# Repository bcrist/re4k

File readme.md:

# Fusemaps for Lattice ispMach4000 CPLDs

This repo contains reverse-engineered fusemaps for most of the commonly available LC4k CPLDs from Lattice.

Data is provided in text files containing machine and human readable S-Expressions describing the fuse locations that control each feature.
These are intended to be used to generate libraries so that CPLD configurations can be created using whatever programming language is desired.
Existing libraries include:

* Zig: [Zig-LC4k](https://github.com/bcrist/Zig-LC4k)
* VHDL: [LC4K Core](https://github.com/devsaurus/lc4k_core)

If you build a library/bindings for another language, let me know so I can list it here!

## Device List

|            |TQFP44|TQFP48|TQFP100|TQFP128|TQFP144|csBGA56|csBGA64|csBGA132|csBGA144|ucBGA64|ucBGA132|
|:-----------|:----:|:----:|:-----:|:-----:|:-----:|:-----:|:-----:|:------:|:------:|:-----:|:------:|
|LC4032V/B/C | ✔️    | ✔️    |       |       |       |       |       |        |        |       |        |
|LC4032ZC    |      | ✔️    |       |       |       | ✔️     |       |        |        |       |        |
|LC4032ZE    |      | ✔️    |       |       |       |       | ✔️     |        |        |       |        |
|LC4064V/B/C | ✔️    | ✔️    | ✔️     |       |       |       |       |        |        |       |        |
|LC4064ZC    |      | ✔️    | ✔️     |       |       | ✔️     |       | ✔️      |        |       |        |
|LC4064ZE    |      | ✔️    | ✔️     |       |       |       | ✔️     |        | ✔️      | ✔️     |        |
|LC4128V     |      |      | ✔️     | ✔️     | ✔️     |       |       |        |        |       |        |
|LC4128B/C   |      |      | ✔️     | ✔️     |       |       |       |        |        |       |        |
|LC4128ZC    |      |      | ✔️     |       |       |       |       | ✔️      |        |       |        |
|LC4128ZE    |      |      | ✔️     |       | ✔️     |       |       |        | ✔️      |       | ✔️      |

LC4256 and larger devices are not supported at this time.
Automotive (LA4xxx) variants likely use the same fusemaps as their LC counterparts, but that's just conjecture.
Please don't use this project for any automotive or other safety-critical application.

## Introduction
Please read through the Lattice datasheet for your device if you have not.
Generally I have tried to use the same terminology for things as is used there.
You can also reference the glossary at the end of this document if you are unsure of what an acronym or term means.
You can find PDF and KiCAD format schematics showing the structure of each type of device in the `schematics` directory.

## General Fusemap Layout
All LC4k devices have a logical layout of fuses into a 2D grid with either 100 or 95 rows,
and a variable number of columns, depending on the number of GLBs in the device.
The JEDEC files list these fuses one row after another,
and when programming the device via JTAG each row is delivered in a separate SDR transaction.

Each GLB uses a chunk of at least 86 columns,
and the GLBs are laid out side-by-side,
however they are not generally ordered from left to right
(the block for GLB "A" is not necessarily to the left of the block for GLB "B").

The first 72 rows contain PT and GI routing fuses.
This part of the fusemap is densely packed;
every single logical fuse corresponds to a bit of FLASH memory and controls the behavior of the device.

The remaining rows have a variety of uses, and are sparsely packed;
most bits don't actually correspond to FLASH memory cells, and always read as a `1`, even after attempting to program them to `0`.

Generally there is a single column corresponding to each macrocell slice, containing fuses that configure that macrocell slice.
These columns are arranged in groups of two, usually with 8 mostly-unused columns separating each pair.
Devices that only have 95 rows only have a single I/O cell per pair of macrocells.
Instead of placing all the I/O cell configuration fuses in the same column,
half of the fuses are shifted over to the adjacent macrocell's column,
reducing the total number of rows needed.

Each GLB has a few bits of block configuration which are placed in the "borders" to the left and right of the macrocell slice columns.
This includes fuses for configuring block clock source/polarity, shared PT polarity, routing of the shared PT enable to the GOE bus, etc.

Finally, global configuration is typically placed in a small, vaguely ring-shaped structure at the right edge of one of the GLB regions.
This includes configuration of input-only pins, GOE polarity, and oscillator/timer (in ZE devices).

## S-Expression Files
The reverse-engineered fusemap for each device consists of a set of s-expression files in `LC4xxx/LC4xxx*_*/.sx`.
There is also a combined file `LC4xxx/LC4xxx*_*.sx` which contains the data from all of the individual files.
The meaning of the data in each particular file is explained below.
If the syntax of any of the files is confusing to you after reading its corresponding section,
please open an issue so I can try to document it better.

### `grp.sx` `(global_routing_pool)`
Each GLB has 36 GI "slots" which (along with their complements) are used as inputs to the product terms in that GLB.
Each GI can be selected from a fixed set of signals in the global routing pool.
The options are different for each GI "slot" in the GLB,
but every GLB in the device uses the same options for the same GI slot.
The number of options for each slot depends on the device type
(devices with more GLBs have more GRP signals,
therefore in order to have multiple possible routings for each signal,
each GLB must have more possible options).

For devices that have an even number of GI options,
the option fuses are stored at the very left side of the GLB block,
using `N/2` columns (where `N` is the number of options).
A "one-cold" encoding is used here; i.e. there is one fuse for each option,
and only one fuse should be programmed to 0 for each GI.

For devices that have an odd number of GI options, the GLBs are organized into pairs,
and each pair shares the same columns of GI routing fuses.  The first row contains fuses
for one of the GLBs, and the second row contains fuses for the other.

### `pterms.sx` `(product_terms)`
Within the first 72 rows, each column
(with the exception of the columns used for GI routing above)
represents a single product term.
Every pair of rows corresponds to a single GI slot,
with the first row representing the non-inverted GI signal,
and the second row representing the inverted version of the same signal.

Programming a fuse within a product term to 0 means the corresponding signal must be asserted
in order for the product term to output `true`.
Another way to think of this is that the fuse value is OR-ed with the signal, and the result is
passed into the product term's AND gate.
Therefore if no PT fuses are set to 0, the PT will always yield `true`.
If both fuses are set to 0 for any GI, the PT will always yield `false`.
When the lpf4k fitter wants to make a PT `false`,
it sets all the fuses for the first dozen or so rowss to 0.
It's not clear why they chose to set just those.
It may be that setting just one pair to 0 might create static hazards
if the GI mapped to that slot changes.
But in that case wouldn't it be best to set all GI pairs to zeroes?
In testing, that does seem to work as expected,
so that's what I'd recommend doing.
My best guess is that this could be a holdover from older device families
that used sense amplifiers instead of fully CMOS logic.
Setting all fuses to 0 might cause higher power usage in such devices.

Product terms are grouped into clusters of 5,
with one cluster associated with each macrocell.
Additionally, there are 3 extra product terms per GLB,
which may be used for specific purposes,
but are shared amongst all macrocells in the GLB.
These PTs are always in the last 3 columns of the GLB's block.

### `cluster_routing.sx` `(cluster_routing)`
Each product term can optionally be used for a special purpose related to that macrocell (see below),
or they can be summed (OR-ed) together and fed into the macrocell's logic input.

Since a logic equation simplified to a sum-of-products often requires more than 5 product terms,
a cluster can either keep it's sum for itself,
or it can "donate" it to one of up to three nearby macrocells.
Each cluster then creates a second sum from any intermediate sums that were routed to that cluster.
A cluster can receive a "donation" (or multiple) even if it is not "keeping" it's own original sum.
Therefore this second sum can represent up to 20 product terms, all with a constant propagation delay.
Some specific clusters have a maximum of < 20 PTs:

* The cluster for MC 0 can only receive a sum from cluster 1 or cluster 2, so including itself it has a maximum of 15 PTs.
* The cluster for MC 14 can only receive a sum from cluster 13 or cluster 15, so including itself it has a maximum of 15 PTs.
* The cluster for MC 15 can only receive a sum from cluster 14, so including itself it has a maximum of 10 PTs.

A cluster sum can only be routed to one other cluster;
it can't be duplicated and sent to multiple neighboring clusters.

### `wide_routing.sx` `(wide_routing)`
In cases where a very large number of product terms are needed,
but very few outputs are needed,
the output of the second sum above can be redirected to the cluster at index `(N+4)%16`
(where `N` is the current cluster index).
This is referred to in the datasheets as "SuperWIDE(tm)" steering logic.

Note that this differs from `cluster_routing` in several ways:

* It "wraps around", so cluster 15 can be routed to cluster 3.
* It can be "chained" such that any macrocell in the GLB can potentially use every PT cluster, if no other MCs in the GLB need a cluster.
* Using this feature increases the maximum propagation delay (but not equally; PTs that go through the wide routing will be slower than those in the final cluster's 20-PT group).

When a macrocell's cluster is routed away to another cluster,
the macrocell sees a constant low (false) value as its logic input.

### `input_bypass.sx` `(macrocell_data)`
A macrocell register's data/toggle input may be configured to come directly from the macrocell's input pad,
instead of having to travel through the GRP, PTs, cluster routing, etc.
This provides a reduced minimum setup time.

Technically this feature can also be used when the macrocell is configured for combinational logic,
but there's not much point in doing so,
since that just makes the macrocell feedback signal the same as the input buffer signal.
You could use an ORM offset to create a tri-state line driver where the input and output are both pins,
and the OE signal is controlled by the CPLD logic.
This would yield the fastest possible propagation delay across the line driver,
but if propagation delay is that critical,
you'd probably be better off just outputting the OE signal and using an external tri-state buffer or bus switch.

### `zerohold.sx` `(zero_hold_time)`
When a macrocell is configured as an input register,
an extra delay can be added to bring the minimum hold time down to 0.
This also means the setup time is increased.
This is controlled by a single fuse that affects the entire chip.
Registers whose data comes from product term logic are not affected by this fuse,
because the internal propagation delays mean that no hold time is required anyway.

### `pt0_xor.sx` `(pt0_xor)`
Each macrocell contains an XOR gate.
The output of the XOR gate goes to the data/toggle input of the macrocell's register,
and optionally to the macrocell feedback/ORM input (when the MC is in combinational mode).

One of the inputs to the XOR gate is always the logic input from the PT cluster router.

The second input of the XOR gate can be either a constant value,
or the result of the macrocell's first product term, PT0.
When it is sourced from PT0, that product term is removed from its cluster sum.
When PT0 is not redirected, a logic 0 is fed to the XOR (optionally inverted; see below).

Note that the datasheets' macrocell schematic (fig. 5)
depicts the input register mux feeding into one of the XOR inputs,
however when testing real devices,
we see that the XOR gate is bypassed completely when the `input_register` fuse is cleared.
This implies that the input register mux is actually located after the XOR output.
This makes sense, since the idea of the input register is to make the setup time as short as possible.

### `invert.sx` `(invert)`
The second input of the XOR gate can be inverted using this fuse.
When sourced from PT0, this means PT0 can be thought as a 36-input OR gate
instead of a 36-input AND gate (via a De Morgan transformation;
you must also use the complement of each PT0 input of course).

When the inverter is enabled, but the XOR is not sourced from PT0,
the second XOR input becomes a constant high,
so the logic sum from the PT cluster router is inverted.
Again, one way to think of this is that you can use the macrocell as a product-of-sums
instead of a sum-of-products.

### `mc_func.sx` `(macrocell_function)`
Each macrocell can implement one of four fundamental circuits:

* Purely combinational logic
* Transparent latch
* D flip-flop
* T flip-flop

The latter 3 all act as single bit storage elements,
and thus have some extra configuration that is irrelevant for combinational macrocells:

* Clock source
* Clock enable source
* Power-up initialization
* Asynchronous set/reset

These features are described below.

### `clock_source.sx` `(clock_source)`
When a macrocell is used as a register,
it needs a clock signal, which can be one of eight options:

* Four block clock signals (see below)
* The GLB's shared clock PT
* The macrocell's PT1
* The macrocell's PT1, inverted
* A constant low/false

When it is sourced from PT1, that product term is removed from its cluster sum.

When the macrocell is configured as a D or T flip flop, the clock triggers on the rising edge.
If if the source can be inverted, it effectively flips it to trigger on the falling edge.

When configured as a latch, it will be transparent when the clock signal is high,
and latched when the clock signal is low.

### `bclk_polarity.sx` `(bclk_polarity)`
The four BCLK clock selection options come from dedicated input pins
(usually four, but some devices only have two).
Using these avoids the need to use macrocell PTs or the GLB's shared clock PT for the clock.
The polarity of these clocks can be configured independently for each GLB.
It is configured in fixed pairs,
where each BCLK can be either the non-inverted version of one of the clocks,
or the inverted version of the _other_ clock.
So you can have both clocks non-inverted, both clocks inverted,
or a complementary pair of either clock.

### `ce_source.sx` `(clock_enable_source)`
The clock enable inhibits the updating of the register contents when it is high.
It has no effect when the macrocell is configured for combinational logic.

For transparent latches, it works effectively as if the clock were ANDed with the CE;
as long as both are high, the latch is in transparent mode;
if either goes low, it latches the current value.

For D and T flip flops, this means as long as the CE is low during the triggering edge,
there will be no change that cycle.
This is not the same as simply ANDing the CE with the clock signal;
the CE does not need to remain low for the entire duration that the clock is high.

There are four possible sources for the CE signal:

* The macrocell's PT2
* The macrocell's PT2, inverted
* The GLB's shared clock PT
* A constant high/true

The shared clock PT is the same one that's used as an option for the clock,
and within a GLB, the same PT can be used as a clock for some MCs and a CE for others.

When it is sourced from PT2, that product term is removed from its cluster sum.
Note that PT2 can also be used for an async set/reset signal (see below).

### `shared_pt_clk_polarity.sx` `(shared_pt_clk_polarity)`
Each GLB's shared clock PT can optionally be inverted.
This affects all usages within the GLB, both as a clock and a clock enable.

### `init_state.sx` `(init_state)`
When a macrocell is configured as a register,
its initial state at power-up can be configured.
This configuration can be selected independently for each macrocell.

### `init_source.sx` `(init_source)`
When a macrocell is configured as a register,
an signal can be used to asynchronously set or reset the register to its power-up state.
While this signal remains high, the macrocell is forced into its power-up state.

There are only two options for the source of this signal:

* The macrocell's PT3
* The GLB's shared init PT

This means that if the GLB's shared init PT is not a constant false,
any registers in that GLB that _don't_ want to use a reset signal must use PT3 as a constant false instead.

It PT3 is used as the source, that product term is removed from its cluster sum.

### `shared_pt_init_polarity.sx` `(shared_pt_init_polarity)`
Each GLB's shared initialization PT can optionally be inverted.

### `async_source.sx` `(async_source)`
An optional second asynchronous set/reset signal can be sourced from PT2.
While the signal remains high, the macrocell is forced into the complement of its power-up state.

Note also that PT2 can also be used as a source for the CE signal,
and while it is possible to simultaneously use it for both,
generally you wouldn't be able to use the same PT logic for both,
so this generally you'd use it for one or the other.

When PT2 is used as an async set/reset, that product term is removed from its cluster sum.

### `pt4_oe.sx` `(pt4_output_enable)`
When this fuse is programmed,
PT4 is removed from the macrocell's cluster sum,
and instead routed to the ORM.
From there it can be selected as an output enable signal for this macrocell's output,
or certain nearby macrocells (see below).

When not used, the OE signal presented to the ORM is a constant false.

### `output_routing.sx` `(output_routing)`
Normally a macrocell slice's I/O cell will output the signal produced by it's corresponding macrocell,
however there is a built-in "output routing multiplexer" (ORM)
that allows limited redirection to take the output signal
from a macrocell offset of up to +7 instead.

Note that this offset wraps around as well, so the I/O for MC 15 can be selected from MC 0-6 as well.

The PT4 OE signal (if used) is also routed from the same MC.

### `output_routing_mode.sx` `(output_routing_mode)`
For non-ZE family devices, the ORM can be bypassed, which slightly decreases the output delay.
Additionally, the entire macrocell logic block can be bypassed if only a combinational logic output is needed,
with a maximum of 5 PTs.
There are several options available:

* Output the normal signal selected by the ORM
* Bypass the ORM and always output the feedback signal from this macrocell, regardless of the ORM configuration
* Output this cluster's 5-PT sum
* Output this cluster's 5-PT sum, inverted

None of these options affect the routing of the PT4 OE signal;
it always goes through the ORM routing.

When one of the 5-PT sum options is used,
the PT cluster is still routed using the normal cluster routing rules as well,
unlike when individual PTs are redirected for a special use.
It's possible to still use the buried macrocell,
but you have to be careful to isolate the original 5-PT cluster sum, e.g.

* Route it to another cluster
* Route another always true cluster in and use PT0 for a single PT macrocell
* Use the buried macrocell as an input register

### `oe_source.sx` `(output_enable_source)`
Each I/O cell's output driver is active when its output enable signal is high.
The OE signal can be selected from one of 8 sources:

* One of 4 global output enables
* The PT4 output enable signal from the ORM
* The PT4 output enable signal from the ORM, inverted
* A constant high (output only)
* A constant low (input only)

### `goes.sx` `(goe_polarity)`
All devices have 4 global OE signals.
The polarity of these signals can be configured globally,
and their source depends on the device.

Sources for LC4032 devices:

* GOE0: Shared PT OE bus bit 0
* GOE1: Shared PT OE bus bit 1
* GOE2: A0 input buffer
* GOE3: B15 input buffer

Sources for other devices:

* GOE0: Selectable; either shared PT OE bus bit 0, or specific input buffer noted in datasheet
* GOE1: Selectable; either shared PT OE bus bit 1, or specific input buffer noted in datasheet
* GOE2: Shared PT OE bus bit 2
* GOE3: Shared PT OE bus bit 3

### `goes.sx` `(shared_pt_oe_bus)`
The shared PT OE bus is a set of 2 or 4 (depending on the device type, as above) global signals
where each bit can be connected to any of the GLBs' shared enable PT
(note this is shared with the power guard feature on ZE devices).

If multiple GLBs are configured to drive the same PT OE bus line,
it will behave as if only the first (lowest numbered) GLB were used.
It might have been convenient if they had summed the PTs in this case,
but alas, for some reason they didn't.

If no GLBs are configured to drive a PT OE bus line,
it is pulled high (if the polarity fuse is 1) or low (if the polarity fuse is 0).
There's really no reason to utilize this though, since each output cell can be
configured for "always output" or "always high impedance" without using any GOE signal.

### `drive.sx` `(drive_type)`
One fuse per output controls whether the output is open-drain or push-pull.

Open-drain can also be emulated by outputing a constant low and using OE to enable or disable it,
but that places a lot of limitation on how much logic can be done in the macrocell;
only a single PT can be routed to the OE signal.

### `slew.sx` `(slew_rate)`
One fuse per output controls the slew rate for that driver.
According to the datasheet,
using the slow slew rate adds approximately 1ns to the output buffer propagation delay,
which means rise and fall times are likely about twice as long as normal.

### `threshold.sx` `(input_threshold)`
The Lattice fitter allows each input signal's voltage standard to be selected from around a half dozen choices, including:
* 1.8V LVCMOS
* 2.5V LVCMOS
* 3.3V LVCMOS
* 3.3V LVTTL (5V-tolerant)
* 3.3V PCI (5V-tolerant)

The datasheets and IBIS models are quite vague about the actual input structure used in the devices,
but it turns out this configuration only affects one fuse per input,
so it seems that this fuse selects either a high or low input transition threshold.
Generally speaking, the high threshold is suitable for either 2.5V or 3.3V signals,
and the low threshold is for 1.8V or 1.5V signals.

Additionally, the datasheet mentions that inputs are only 5V-tolerant when V<sub>CCO</sub> is 3.3V,
so the protection diodes probably clamp relative to that rail rather than V<sub>CC</sub>.

The following are mostly guesses for the actual V<sub>th</sub> based on the published limits in the datasheet,
and assuming that the threshold is always referenced to V<sub>CC</sub>,
as opposed to using V<sub>CCO</sub> or an internal fixed voltage reference.

| V<sub>th</sub> | `-V`                      | `-B`                      | `-C`/`-ZC`                  | `-ZE`                    |
|:---------------|:-------------------------:|:-------------------------:|:---------------------------:|:------------------------:|
| low            | 0.28&times;V<sub>CC</sub> | 0.36&times;V<sub>CC</sub> | 0.5&times;V<sub>CC</sub>    | 0.5&times;V<sub>CC</sub> |
| high           | 0.4&times;V<sub>CC</sub>  | 0.5&times;V<sub>CC</sub>  | 0.73&times;V<sub>CC</sub>   | 0.68&times;V<sub>CC</sub> (falling edge)<br>0.79&times;V<sub>CC</sub> (rising edge) |

### `bus_maintenance.sx` `(bus_maintenance)`
2 fuses allow selection of one of four input termination options:
    * pull up
    * pull down
    * bus-hold
    * floating/high-Z
In ZE family devices, this can be configured separately for each input pin.
In other families, there is only a single set of fuses which apply to the entire device.

### `bus_maintenance.sx` `(bus_maintenance_extra)`
On certain non-ZE devices,
setting bus maintenance to floating causes the fitter to toggle additional fuses
beyond the two global bus maintenance fuses.
This only happens on devices where the die has I/O cells that aren't bonded to any package pin. (e.g. TQFP-44 packages)
Normally, these extra I/O cells are left as inputs,
but if inputs are allowed to float, this could cause excessive power usage,
so the fitter turns them into outputs by setting the appropriate OE mux fuses.

### `power_guard.sx` `(power_guard)`
In ZE-family devices, input signals can be "masked"
so that high frequency signals don't propagate very far through the chip when not needed.
This can reduce dynamic power consumption.
Normally, power guard is disabled when the GLB's shared enable PT is high.
Power guard can also be permanently disabled for individual inputs using a fuse defined here.
That may be necessary if you need to use the shared enable PT for a GOE.

### `osctimer.sx` `(osctimer)`
ZE-family devices contain a low-accuracy 5 MHz oscillator,
and a divider that can drop it down to lower frequencies.
When enabled, these signals replace the macrocell feedback signals for specific macrocells.

# Fitter Bugs & Uncertainties

In the process of trying to get the LPF4k fitter to do what I want,
I've encountered a handful of bugs,
as well as some limitations which make it impossible to exercise certain hardware features.
In these cases, I've done my best to manually reverse engineer with real hardware,
but I don't have access to every device variant,
so I've also had to make some assumptions.
I'll try to document those here.

### Fitter won't route all GOEs
Even though there are four GOEs in every device,
the fitter will never route more than two of them in any particular design.
If you add more unique equations than that,
it'll start using PT4 as individual OE for the extra ones.
I tried adding a bunch of dummy logic product terms so that there isn't a free PT available,
but that doesn't convince it to do otherwise;
it'll just shout about failing to allocate everything.

It's also impossible to force the fitter to place a shared PT OE in a specific GLB.
This means I've had to make some assumptions about the locations of the shared PT OE bus fuses,
but based on testing with LC4032ZE and LC4064ZC devices,
I would be surprised if they don't hold for all devices.

### Negated GOE signals
When attempting to use a suffix of `.OE-` to create an active-low GOE,
the fitter report lists the correct equations,
but the JEDEC file that results is identical to one that just used `.OE`.
In order to coerce it to actually program the GOE polarity fuse,
you can invert the source signal instead,
but that only works when it's coming directly from an OE pin.
Otherwise it will just use the complemented signal in the shared PT OE.
This means it's really only possible to locate two of the GOE polarity fuses per device.
We have to infer the locations of the others by assuming that they're all in a contiguous block.

### Fitter won't set shared PT init polarity
Somewhat similar to the bug above,
the fitter will refuse to route a design that uses `.AR-` or `.AS-`.
Presumably this is because it's not able to invert the output of PT3 when that's used for initialization.
But when coming from the shared PT, there _is_ a configurable polarity;
it's just impossible to get the fitter to use it.
As above, if you invert a single signal, it will just encode that in the shared PT itself.
So again, we have to infer the location of this fuse based on where we know the shared PT clock polarity fuse is,
with hardware testing for verification.

### LC4128ZE_TQFP100 Missing Power Guard fuse for CLK0
Enabling a power guard instance for this pin on this particular device does not cause any fuse to be written.
The fitter does not give any warnings however,
and the dedicated clock power guard fuses for other package variants match this one,
except for this one fuse.
This leads me to assume that one line in the fitter source code probably got deleted or something,
causing it to skip this fuse.
I added a special case to force this to the fuse it (very likely) should be.

### LC4064ZC_csBGA56 Dedicated Inputs
The datasheet lists that this device has 32 I/Os and 12 input-only pins (4 clocks and 8 dedicated inputs).
I believe that two of the 8 dedicated inputs are actually just connected to regular macrocells.

There is quite a bit of evidence supporting this assumption:
* No other LC4064 or LC4128 packages have more than 6 dedicated inputs, even though some devices (e.g. `LC4064ZC_csBGA132`) have unconnected pins.  One would think if the die actually had 8 dedicated inputs, they would connect them to pins when possible.
* The LC4064s in TQFP-44 use a trick where only half the macrocells have corresponding I/O cells, resulting in a reduced JEDEC height of 95, but this device has a JEDEC height of 100, so internally it likely has the full complement of 64 I/O cells, with half of them unconnected.
* The GI routing fuses used for ball F8 are exactly the same as the fuses for macrocell C12's I/O in packages that expose it.
* The GI routing fuses used for ball E3 are exactly the same as the fuses for macrocell A15's I/O in packages that expose it.

Therefore, in the `pins.csv` file, I've listed balls E3 and F8 as I/Os corresponding to macrocells A15 and C12, respectively.
Attempting to assign these pins as outputs causes the fitter to spit out a warning,
so there are some fuses that I can't reverse engineer using the fitter.
In these cases I'm just copying the fuse locations from the corresponding macrocell in the `LC4064ZC_TQFP100` package,
under the assumption that it uses the same die.

Additionally, there appears to be a fitter bug relating to the input threshold fuse for balls F8 and E1.
The fitter toggles two input threshold fuses for the input on ball E1,
and no fuses for the input on ball F8.
Since F8 is one of the "weird" dedicated inputs,
I'm using the C12 macrocell's input threshold fuse from the TQFP100 package for that one,
just like I do for the output configuration fuses.
Then I can just exclude that fuse from the fuses the fitter toggled for ball E1,
which yields only one remaining correct fuse for that ball.

I don't have any of these devices to test physically, so to be safe,
you may just want to avoid using balls E1, E3, and F8 entirely for this particular device.

### Fitter Report missing GI data
For `LC4064ZC_csBGA56`, the second column (GIs 18-35) doesn't always show up in the fitter GI summary.
For some other devices, "input only" pins are incorrectly listed as sourced from a macrocell feedback signal.
e.g. for `LC4128ZC_TQFP100`, pin 12's source is listed as "mc B-11",
but the GI mux fuse that's set is one of the ones corresponding to pin 16 in `LC4128V_TQFP144`;
which is MC B14 and ORP B^11 in that device.
So it seems the fitter is writing the I/O cell's ID in this case, rather than the actual pin number.

## Glossary

#### GLB
Generic Logic Block: A group of 36 GIs, 83 PTs, 16 MCs, and the other logic associated with them.  Each device contains two or more GLBs.

#### GRP
Global Routing Pool: the set of all signals that can be used as inputs to a GLB.  This includes all I/O cell pins, feedback from all MCs, dedicated clock pins, and (in some devices) dedicated input pins.

#### GI
Generic Input: One of 36 signals per GLB which can be used in that GLB's product terms.

#### PT
Product Term: Up to 36 signals (or their complements) ANDed together.

#### MC
Macrocell: A single flip-flop or combinational logic "output".

#### MC Slice
Macrocell Slice: A 5-PT cluster, macrocell, routing logic, and I/O cell.  Each GLB contains 16 MC Slices, along with the 3 shared PTs, BCLK and GI configuration.

#### ORM
Output Routing Multiplexer: Allows macrocells and their associated OE product term to be shunted to a different nearby pin.

#### BCLK
Block Clock: Each GLB ("Block") can independently configure the polarity of the dedicated clock inputs.

#### BIE
Block Input Enable: For ZE-family devices, inputs can be dynamically masked to reduce dynamic power consumption.

#### GOE
Global Output Enable: Up to four signals which can come from specific input pins, or from the BIE shared PTs.

#### CE
Clock Enable

#### LE
Latch Enable

#### AS
Asynchronous (pre)Set

#### AR
Asynchronous Reset/clear

## Reproduction Steps

In case you want to try to add other devices, or just want to reproduce the .sx files that are committed here, you can follow these build steps:

1. Make sure ispLEVER Classic 2.1 is installed at `C:\ispLEVER_Classic2_1` and that you have a valid license.  In particular, `C:\ispLEVER_Classic2_1\ispcpld\bin\lpf4k.exe` needs to work, but nothing else is used.
2. Make sure Zig is installed and run `zig build -Doptimize=ReleaseSafe` from the `generate/` directory.
3. (optional) Make sure LIMP is installed and run `limp -R .` from the root of the repo.  This will regenerate the Ninja makefiles.
4. Make sure Ninja is installed and run `ninja` from the root of the repo.

Note: a large number of temporary files are created (and then deleted) in the `temp/` directory.  I found that adding a Windows Defender exclusion for the repo and the `ispLEVER_Classic2_1` directory significantly speeds up the process.

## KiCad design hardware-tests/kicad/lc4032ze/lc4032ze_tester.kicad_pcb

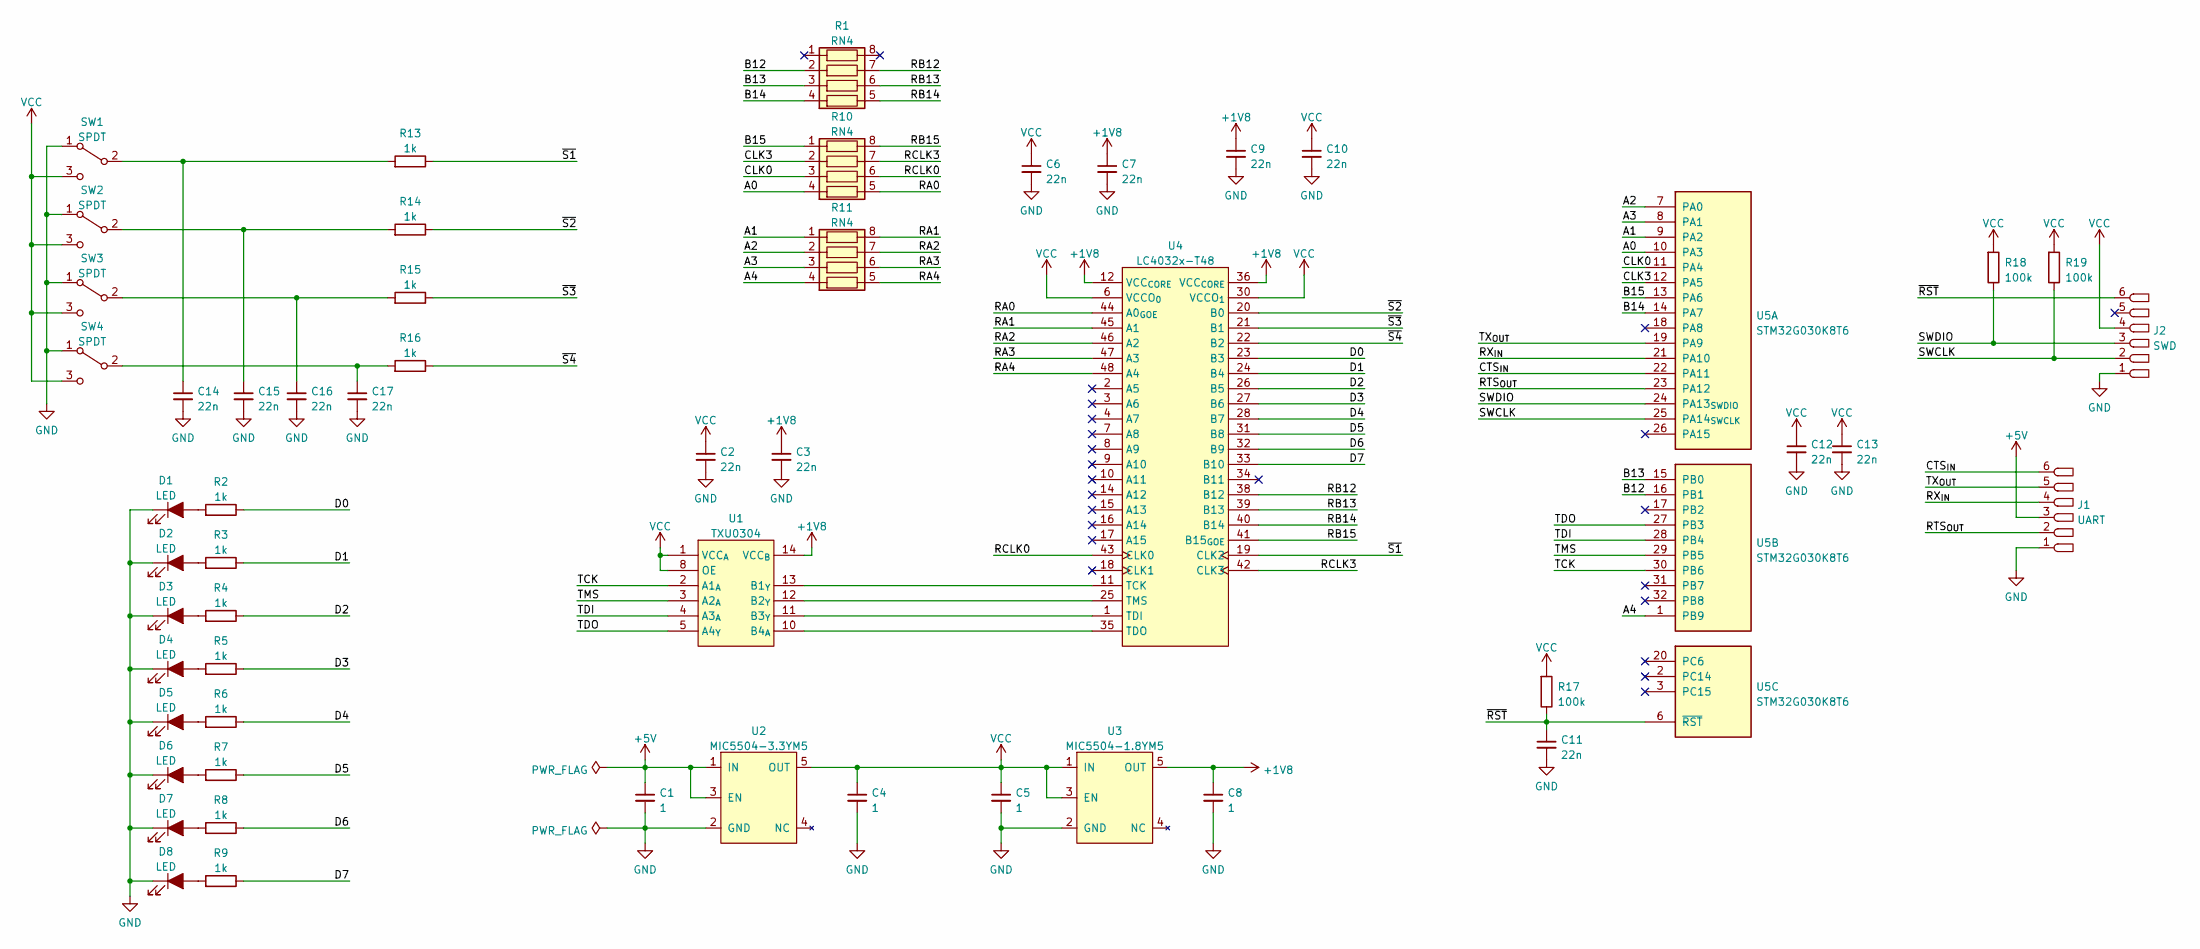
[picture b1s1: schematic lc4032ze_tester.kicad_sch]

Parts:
C1, C4, C5, C8: 1; C_0603
C2, C3, C6, C7, C9, C10, C11, C12, C13, C14, C15, C16, C17: 22n; C_0603
D1, D2, D3, D4, D5, D6, D7, D8: LED; LED_D5.0mm
J1: UART; header_1x6
J2: SWD; header_1x6
R1, R10, R11: RN4; R_0408-8
R2, R3, R4, R5, R6, R7, R8, R9, R13, R14, R15, R16: 1k; R_0603
R17, R18, R19: 100k; R_0603
SW1, SW2, SW3, SW4: SPDT; SW_DIP-6
U1: TXU0304; U_TSSOP-14_4.4x5_P0.65
U2: MIC5504-3.3YM5; U_SOT23-5
U3: MIC5504-1.8YM5; U_SOT23-5
U4: LC4032x-T48; U_QFP-48_7x7_P0.5
U5: STM32G030K8T6; U_QFP-32_7x7_P0.8

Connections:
+1V8: C3.1, C7.1, C8.1, C9.1, U1.14 (VCC_{B}), U3.5 (OUT), U4.12 (VCC_{CORE}), U4.36 (VCC_{CORE})
+5V: C1.1, J1.3, U2.1 (IN), U2.3 (EN)
/A0: R10.4, U5.10 (PA3)
/A1: R11.1, U5.9 (PA2)
/A2: R11.2, U5.7 (PA0)
/A3: R11.3, U5.8 (PA1)
/A4: R11.4, U5.1 (PB9)
/B12: R1.2, U5.16 (PB1)
/B13: R1.3, U5.15 (PB0)
/B14: R1.4, U5.14 (PA7)
/B15: R10.1, U5.13 (PA6)
/CLK0: R10.3, U5.11 (PA4)
/CLK3: R10.2, U5.12 (PA5)
/CTS_{IN}: J1.6, U5.22 (PA11)
/D0: R2.2, U4.23 (B3)
/D1: R3.2, U4.24 (B4)
/D2: R4.2, U4.26 (B5)
/D3: R5.2, U4.27 (B6)
/D4: R6.2, U4.28 (B7)
/D5: R7.2, U4.31 (B8)
/D6: R8.2, U4.32 (B9)
/D7: R9.2, U4.33 (B10)
/RA0: R10.5, U4.44 (A0_{GOE})
/RA1: R11.8, U4.45 (A1)
/RA2: R11.7, U4.46 (A2)
/RA3: R11.6, U4.47 (A3)
/RA4: R11.5, U4.48 (A4)
/RB12: R1.7, U4.38 (B12)
/RB13: R1.6, U4.39 (B13)
/RB14: R1.5, U4.40 (B14)
/RB15: R10.8, U4.41 (B15_{GOE})
/RCLK0: R10.6, U4.43 (CLK0)
/RCLK3: R10.7, U4.42 (CLK3)
/RTS_{OUT}: J1.2, U5.23 (PA12)
/RX_{IN}: J1.4, U5.21 (PA10)
/SWCLK: J2.2, R19.2, U5.25 (PA14_{SWCLK})
/SWDIO: J2.3, R18.2, U5.24 (PA13_{SWDIO})
/TCK: U1.2 (A1_{A}), U5.30 (PB6)
/TDI: U1.4 (A3_{A}), U5.28 (PB4)
/TDO: U1.5 (A4_{Y}), U5.27 (PB3)
/TMS: U1.3 (A2_{A}), U5.29 (PB5)
/TX_{OUT}: J1.5, U5.19 (PA9)
/~RST: C11.1, J2.6, R17.2, U5.6 (~RST)
/~S1: R13.2, U4.19 (CLK2)
/~S2: R14.2, U4.20 (B0)
/~S3: R15.2, U4.21 (B1)
/~S4: R16.2, U4.22 (B2)
GND: C1.2, C2.2, C3.2, C4.2, C5.2, C6.2, C7.2, C8.2, C9.2, C10.2, C11.2, C12.2, C13.2, C14.2, C15.2, C16.2, C17.2, D1.1 (K), D2.1 (K), D3.1 (K), D4.1 (K), D5.1 (K), D6.1 (K), D7.1 (K), D8.1 (K), J1.1, J2.1, SW1.1 (A), SW2.1 (A), SW3.1 (A), SW4.1 (A), U1.7 (GND), U2.2 (GND), U3.2 (GND), U4.5 (GND), U4.13 (GND), U4.29 (GND), U4.37 (GND), U5.5 (GND)
unnamed: C14.1, R13.1, SW1.2 (B)
unnamed: C15.1, R14.1, SW2.2 (B)
unnamed: C16.1, R15.1, SW3.2 (B)
unnamed: C17.1, R16.1, SW4.2 (B)
unnamed: D1.2 (A), R2.1
unnamed: D2.2 (A), R3.1
unnamed: D3.2 (A), R4.1
unnamed: D4.2 (A), R5.1
unnamed: D5.2 (A), R6.1
unnamed: D6.2 (A), R7.1
unnamed: D7.2 (A), R8.1
unnamed: D8.2 (A), R9.1
unnamed: U1.10 (B4_{A}), U4.35 (TDO)
unnamed: U1.11 (B3_{Y}), U4.1 (TDI)
unnamed: U1.12 (B2_{Y}), U4.25 (TMS)
unnamed: U1.13 (B1_{Y}), U4.11 (TCK)
VCC: C2.1, C4.1, C5.1, C6.1, C10.1, C12.1, C13.1, J2.4, R17.1, R18.1, R19.1, SW1.3 (C), SW2.3 (C), SW3.3 (C), SW4.3 (C), U1.1 (VCC_{A}), U1.8 (OE), U2.5 (OUT), U3.1 (IN), U3.3 (EN), U4.6 (VCCO_{0}), U4.30 (VCCO_{1}), U5.4 (VCC)

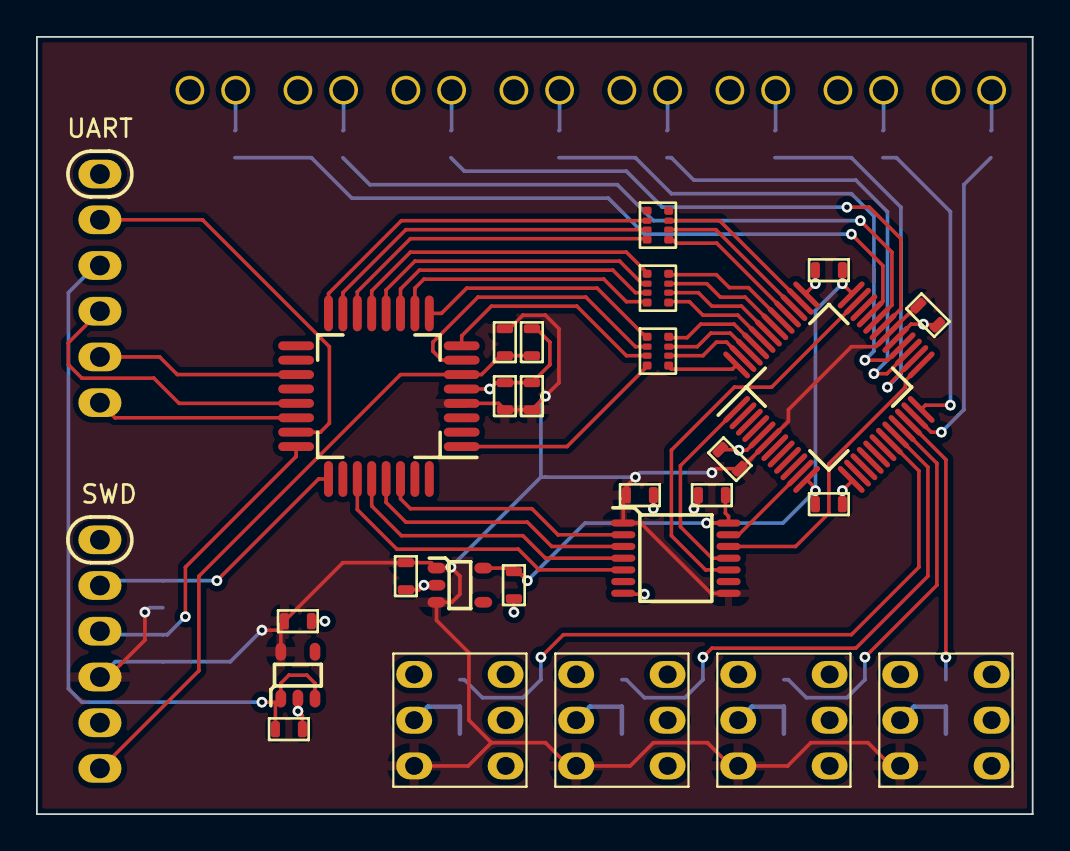
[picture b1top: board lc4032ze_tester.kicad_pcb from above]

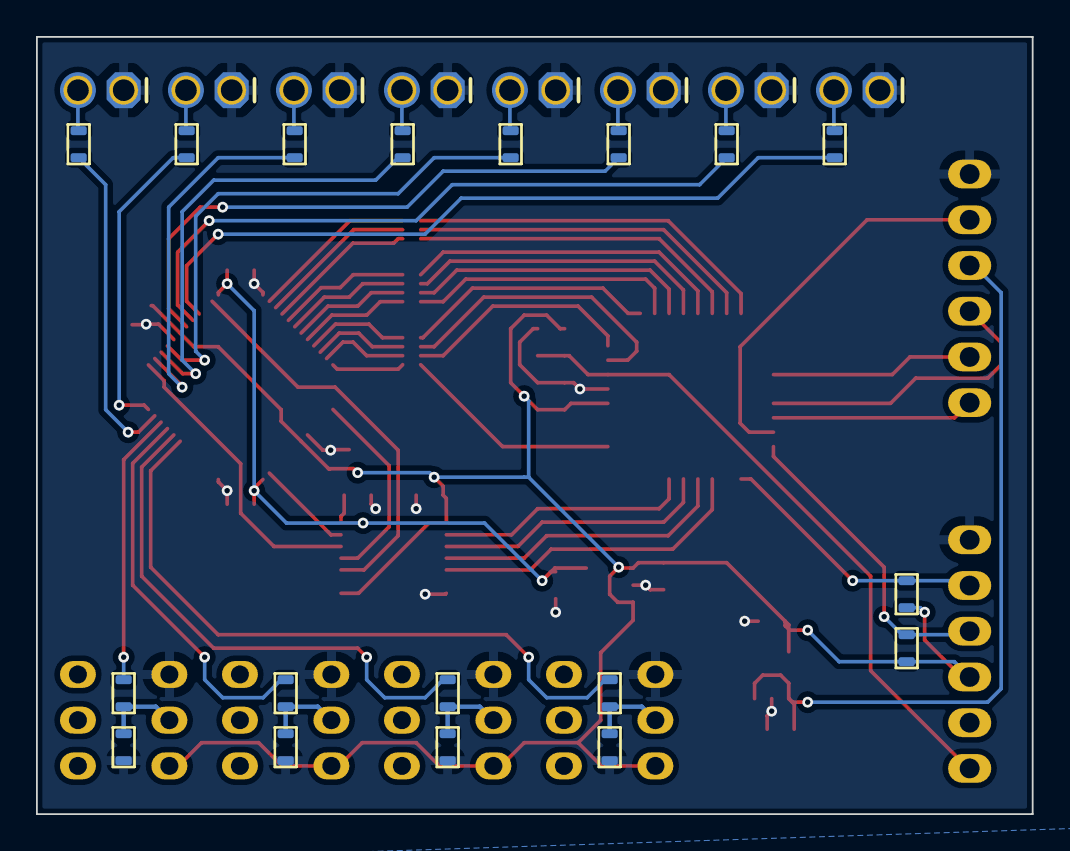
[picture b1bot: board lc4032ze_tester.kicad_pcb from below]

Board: 2 copper layers, 55.3 x 43.2 mm, 54 parts (18 on the bottom side), 65 nets.
